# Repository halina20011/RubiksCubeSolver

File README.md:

# RubiksCubeSolver
silly Rubik's Cube solver that will stand next to my desk and obsessively solve and scramble the cube, helping me procrastinate more by staring at it...

### PCB
2 layer board made with KiCad

### cube solving algorithms
> TODO

### BOM
> TODO

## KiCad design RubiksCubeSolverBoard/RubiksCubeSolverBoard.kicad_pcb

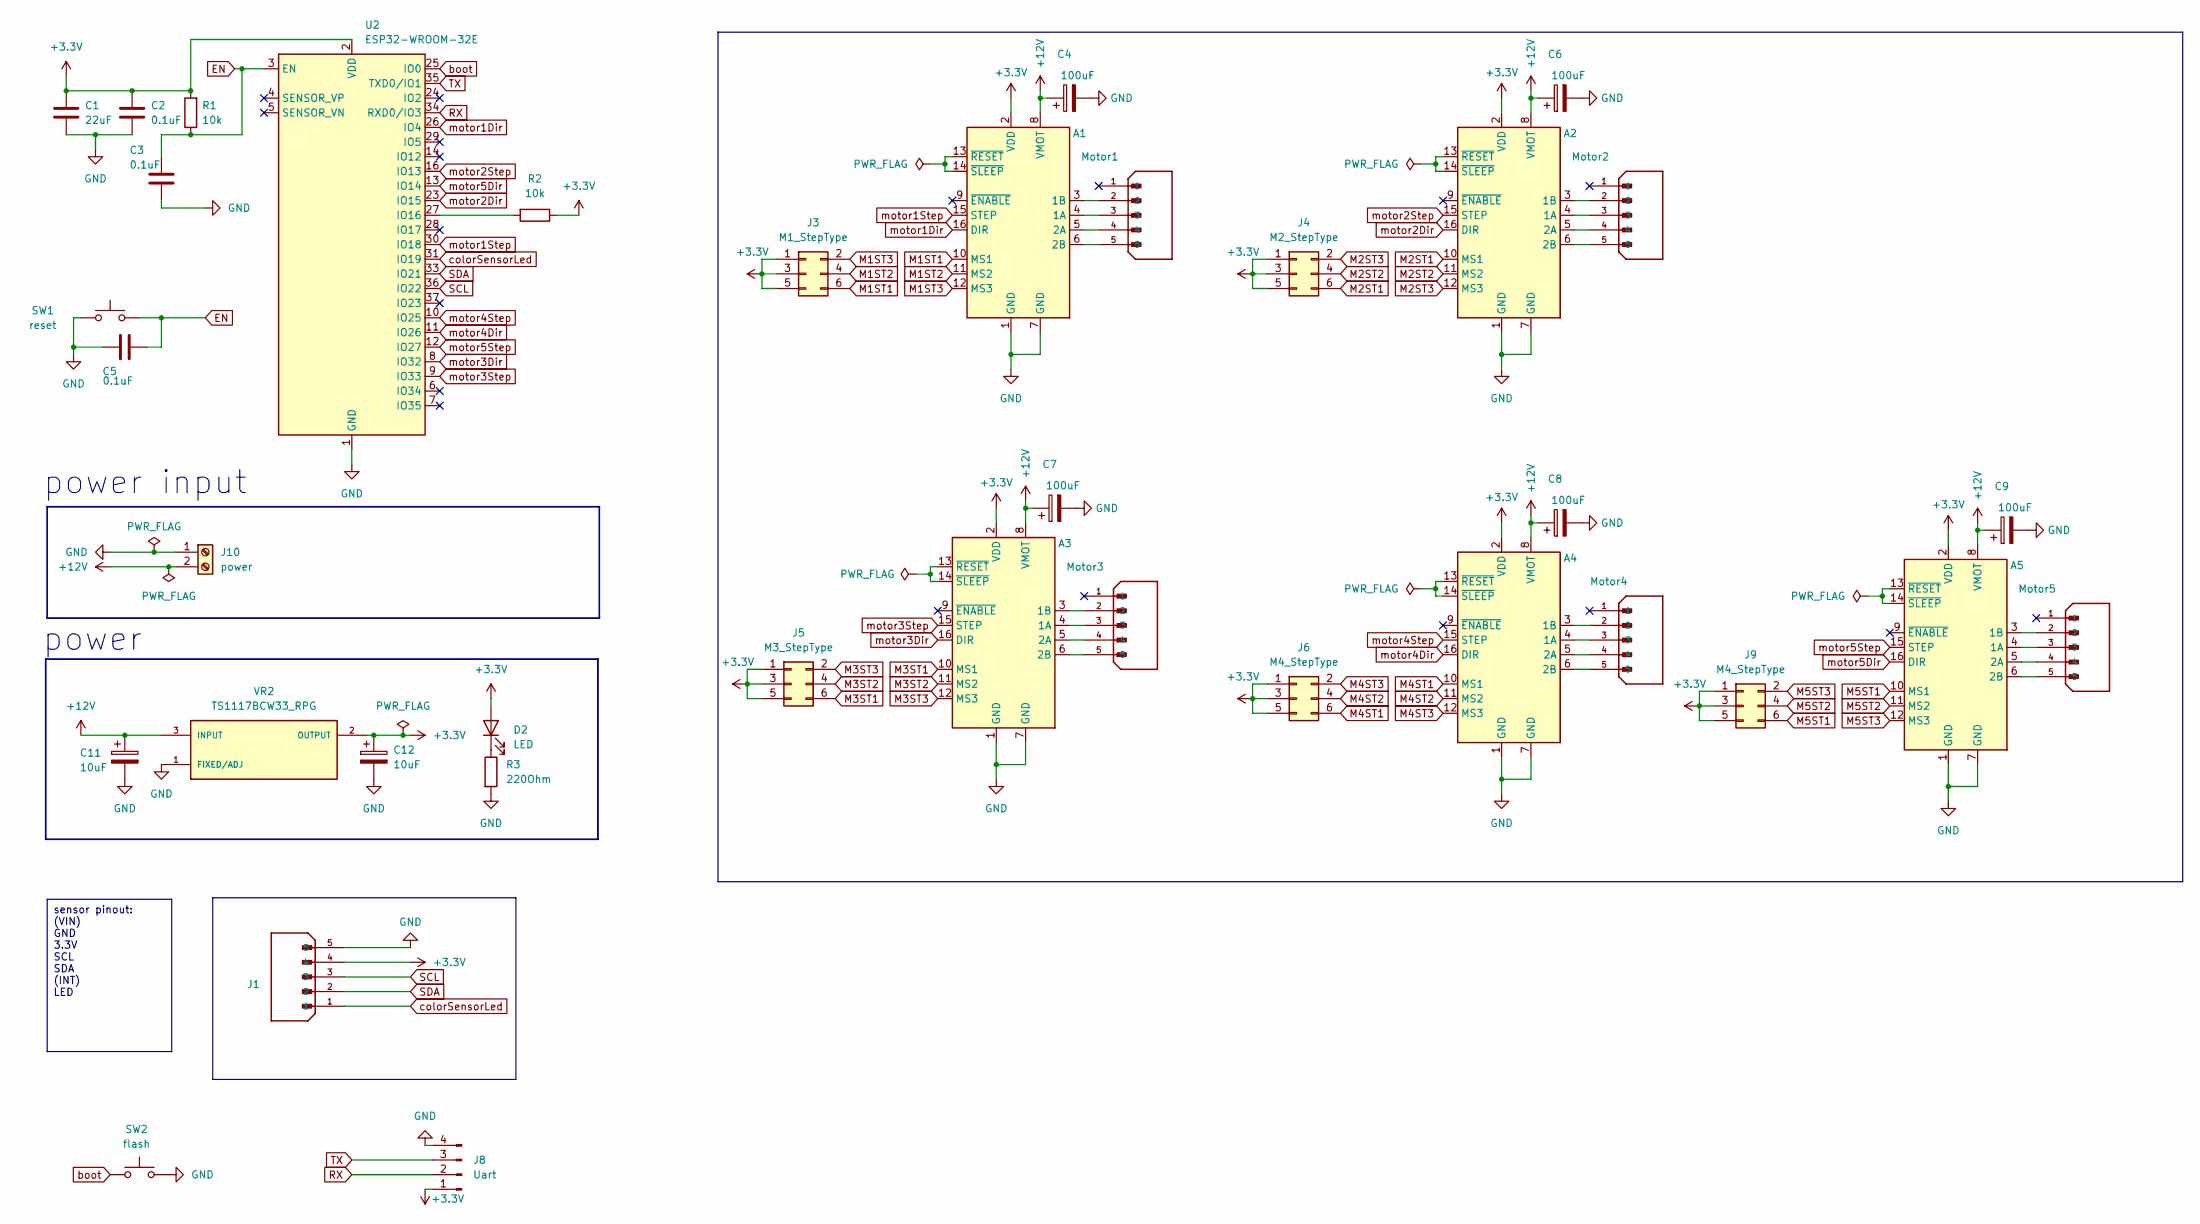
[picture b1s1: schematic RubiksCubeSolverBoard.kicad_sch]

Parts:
A1, A2, A3, A4, A5: Pololu_Breakout_A4988; A4988Mirrored
C1: 22uF; C_0805_2012Metric
C2, C3, C5: 0.1uF; C_0805_2012Metric
C4, C6, C7, C8, C9: 100uF; CP_Elec_6.3x7.7
C11, C12: 10uF; CP_Elec_4x5.4
D2: LED; LED_1206_3216Metric_Pad1.42x1.75mm_HandSolder
J1: colorSensor; JST_B5B-XH-A_LF__SN_; PARTREV N/A
J3: M1_StepType; PinHeader_2x03_P2.54mm_Vertical
J4: M2_StepType; PinHeader_2x03_P2.54mm_Vertical
J5: M3_StepType; PinHeader_2x03_P2.54mm_Vertical
J6, J9: M4_StepType; PinHeader_2x03_P2.54mm_Vertical
J7: Motor1; JST_B5B-XH-A_LF__SN_; PARTREV N/A
J8: Uart; PinHeader_1x04_P2.54mm_Vertical
J10: power; CONN-TH_DB301V-3.5-2P-GN
J14: Motor2; JST_B5B-XH-A_LF__SN_; PARTREV N/A
J18: Motor3; JST_B5B-XH-A_LF__SN_; PARTREV N/A
J22: Motor4; JST_B5B-XH-A_LF__SN_; PARTREV N/A
J26: Motor5; JST_B5B-XH-A_LF__SN_; PARTREV N/A
R1, R2: 10k; R_0805_2012Metric
R3: 220Ohm; R_0805_2012Metric
SW1: reset; SW_Push_SPST_NO_Alps_SKRK
SW2: flash; SW_Push_SPST_NO_Alps_SKRK
U2: ESP32-WROOM-32E; ESP32-WROOM-32D
VR2: TS1117BCW33_RPG; VREG_TS1117BCW33_RPG; PARTREV H1607

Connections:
+3.3V: A1.2 (VDD), A2.2 (VDD), A3.2 (VDD), A4.2 (VDD), A5.2 (VDD), C1.1, C2.1, C12.1, D2.2 (A), J1.4, J3.1, J3.3, J3.5, J4.1, J4.3, J4.5, J5.1, J5.3, J5.5, J6.1, J6.3, J6.5, J8.1, J9.1, J9.3, J9.5, R1.2, R2.1, U2.2 (VDD), VR2.2 (OUTPUT)
+12V: A1.8 (VMOT), A2.8 (VMOT), A3.8 (VMOT), A4.8 (VMOT), A5.8 (VMOT), C4.1, C6.1, C7.1, C8.1, C9.1, C11.1, J10.2, VR2.3 (INPUT)
EN: C3.1, C5.2, R1.1, SW1.2, U2.3 (EN)
GND: A1.1 (GND), A1.7 (GND), A2.1 (GND), A2.7 (GND), A3.1 (GND), A3.7 (GND), A4.1 (GND), A4.7 (GND), A5.1 (GND), A5.7 (GND), C1.2, C2.2, C3.2, C4.2, C5.1, C6.2, C7.2, C8.2, C9.2, C11.2, C12.2, J1.5, J8.4, J10.1, R3.2, SW1.1, SW2.2, U2.1 (GND), U2.15 (GND), U2.38 (GND), U2.39 (GND), VR2.1 (FIXED/ADJ)
M1ST1: A1.10 (MS1), J3.6
M1ST2: A1.11 (MS2), J3.4
M1ST3: A1.12 (MS3), J3.2
M2ST1: A2.10 (MS1), J4.6
M2ST2: A2.11 (MS2), J4.4
M2ST3: A2.12 (MS3), J4.2
M3ST1: A3.10 (MS1), J5.6
M3ST2: A3.11 (MS2), J5.4
M3ST3: A3.12 (MS3), J5.2
M4ST1: A4.10 (MS1), J6.6
M4ST2: A4.11 (MS2), J6.4
M4ST3: A4.12 (MS3), J6.2
M5ST1: A5.10 (MS1), J9.6
M5ST2: A5.11 (MS2), J9.4
M5ST3: A5.12 (MS3), J9.2
unnamed: A1.4 (1A), J7.3
unnamed: A1.3 (1B), J7.2
unnamed: A1.5 (2A), J7.4
unnamed: A1.6 (2B), J7.5
unnamed: A1.13 (~RESET), A1.14 (~SLEEP)
unnamed: A2.4 (1A), J14.3
unnamed: A2.3 (1B), J14.2
unnamed: A2.5 (2A), J14.4
unnamed: A2.6 (2B), J14.5
unnamed: A2.13 (~RESET), A2.14 (~SLEEP)
unnamed: A3.4 (1A), J18.3
unnamed: A3.3 (1B), J18.2
unnamed: A3.5 (2A), J18.4
unnamed: A3.6 (2B), J18.5
unnamed: A3.13 (~RESET), A3.14 (~SLEEP)
unnamed: A4.4 (1A), J22.3
unnamed: A4.3 (1B), J22.2
unnamed: A4.5 (2A), J22.4
unnamed: A4.6 (2B), J22.5
unnamed: A4.13 (~RESET), A4.14 (~SLEEP)
unnamed: A5.4 (1A), J26.3
unnamed: A5.3 (1B), J26.2
unnamed: A5.5 (2A), J26.4
unnamed: A5.6 (2B), J26.5
unnamed: A5.13 (~RESET), A5.14 (~SLEEP)
unnamed: D2.1 (K), R3.1
unnamed: R2.2, U2.27 (IO16)
RX: J8.2, U2.34 (RXD0/IO3)
SCL: J1.3, U2.36 (IO22)
SDA: J1.2, U2.33 (IO21)
TX: J8.3, U2.35 (TXD0/IO1)
boot: SW2.1, U2.25 (IO0)
colorSensorLed: J1.1, U2.31 (IO19)
motor1Dir: A1.16 (DIR), U2.26 (IO4)
motor1Step: A1.15 (STEP), U2.30 (IO18)
motor2Dir: A2.16 (DIR), U2.23 (IO15)
motor2Step: A2.15 (STEP), U2.16 (IO13)
motor3Dir: A3.16 (DIR), U2.8 (IO32)
motor3Step: A3.15 (STEP), U2.9 (IO33)
motor4Dir: A4.16 (DIR), U2.11 (IO26)
motor4Step: A4.15 (STEP), U2.10 (IO25)
motor5Dir: A5.16 (DIR), U2.13 (IO14)
motor5Step: A5.15 (STEP), U2.12 (IO27)

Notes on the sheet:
sensor pinout: (VIN) GND 3.3V SCL SDA (INT) LED
power input
power

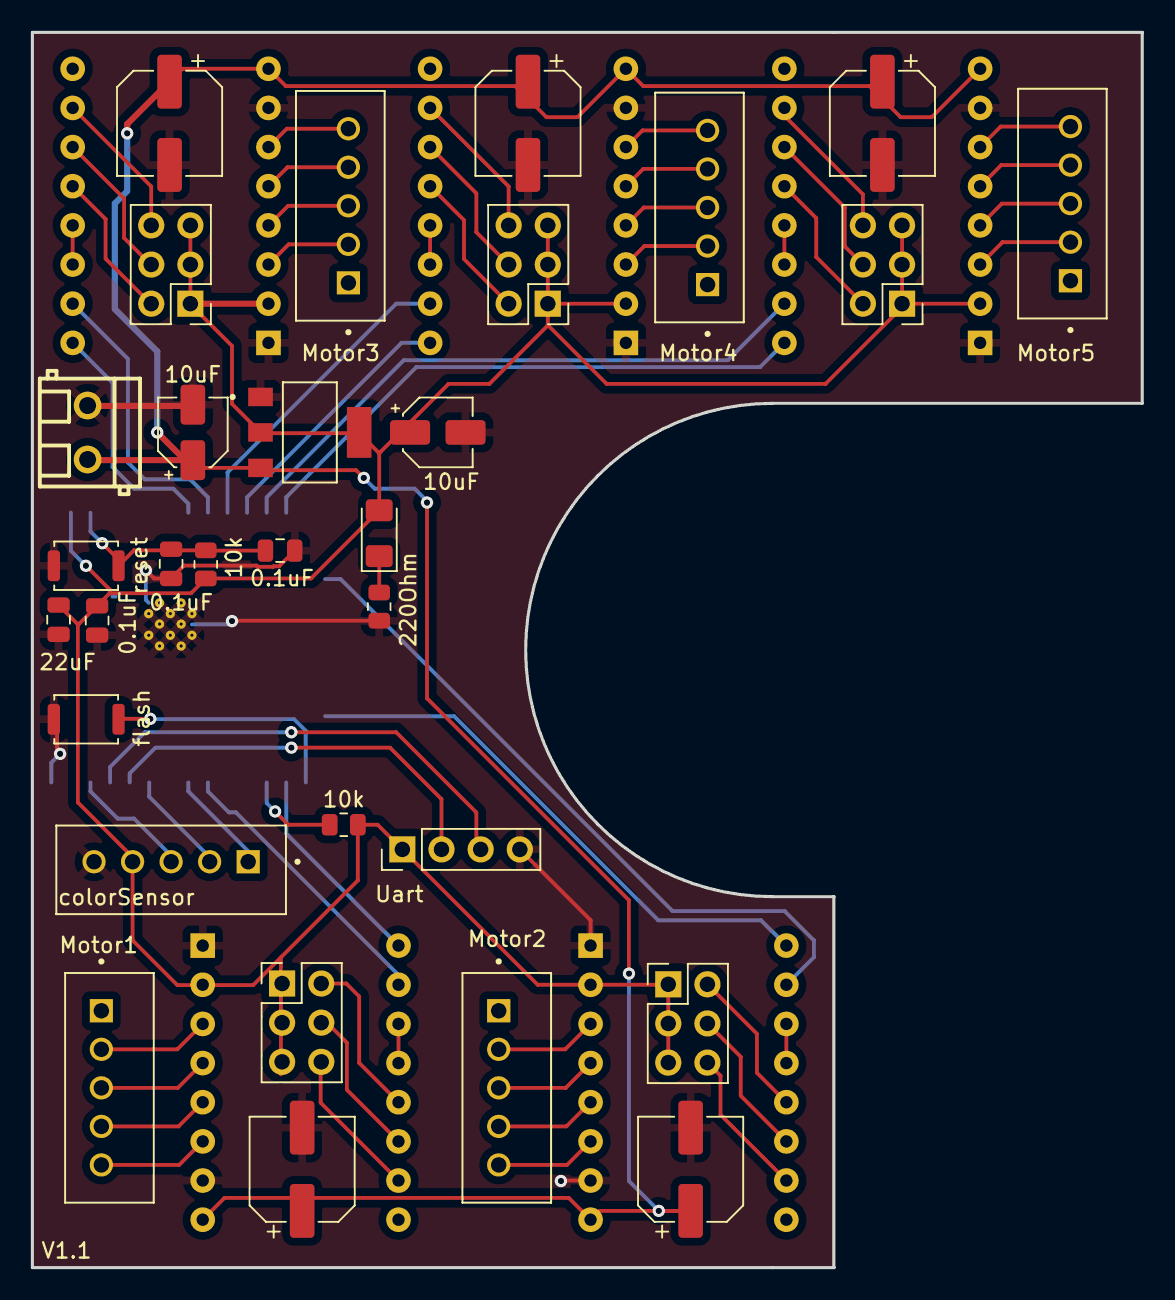
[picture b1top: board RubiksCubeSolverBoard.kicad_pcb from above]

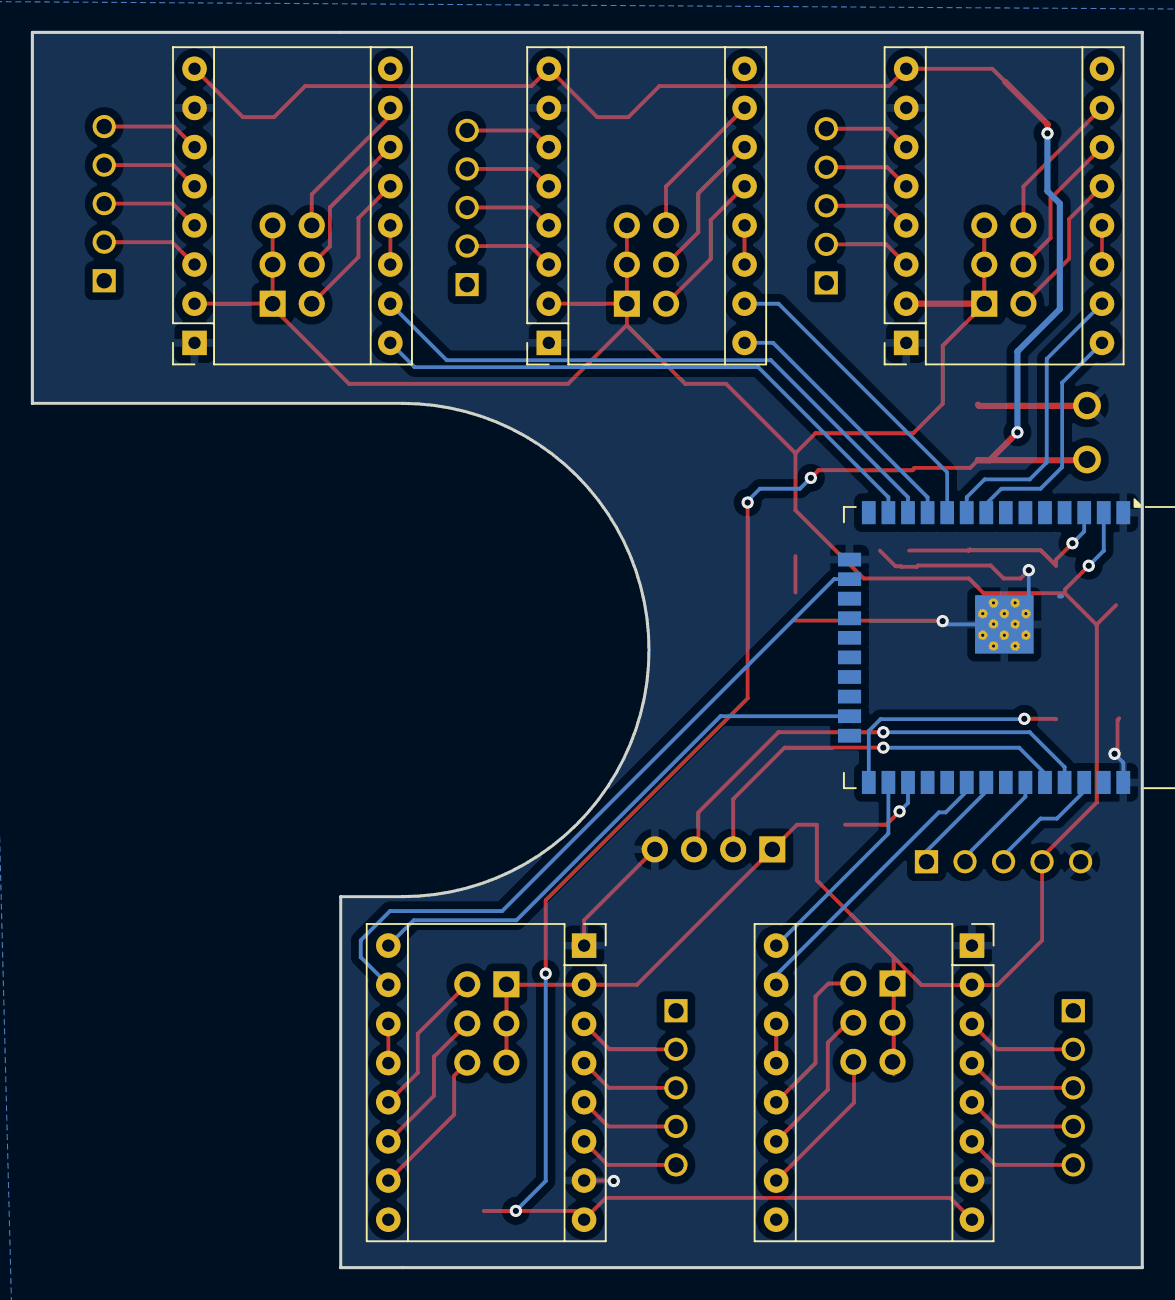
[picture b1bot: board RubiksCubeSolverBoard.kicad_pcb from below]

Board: 2 copper layers, 72.0 x 80.1 mm, 37 parts (6 on the bottom side), 62 nets.

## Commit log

2024-04-08 initial
2024-04-13 webgl2 + cube
2024-04-17 LICENSE
2024-09-25 1 layer board
2024-10-08 2 layer pcb
2024-11-01 pcb v1.1
2024-11-02 controlling stepper motors (delay func)
2024-11-08 web js version
2024-11-17 modeling + exported file + stl files
2025-01-12 color sensor + socket primitive command parser
2025-01-14 switched to websockets
